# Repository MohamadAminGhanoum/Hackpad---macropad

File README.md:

# Hackpad---macropad
I want to build a hackpad or macropad that i can use when watching yt videos or social media. This will help me for when watching and when editing content.
I have spent around 4.5 hours to do this, it took some time to get used to fusion 360 because it is my first time using it.

Note: there are two distinct files for the .step file, one for the top and one for the bottom

websites used to make the layout of buttons:
https://kbplate.ai03.com/
https://www.keyboard-layout-editor.com/#/

BOM - Components used:
- 4 keys
- 1 xiao rp2040-DIP
- 1 oled panel
- 4 sk6812MINI LEDs
- 1x pcb: price: 1.5 dollar
- 1x soldering iron: price: 2USD

Final look of the macropad:

I rendered the files in fusion 360, and the result is as follows,

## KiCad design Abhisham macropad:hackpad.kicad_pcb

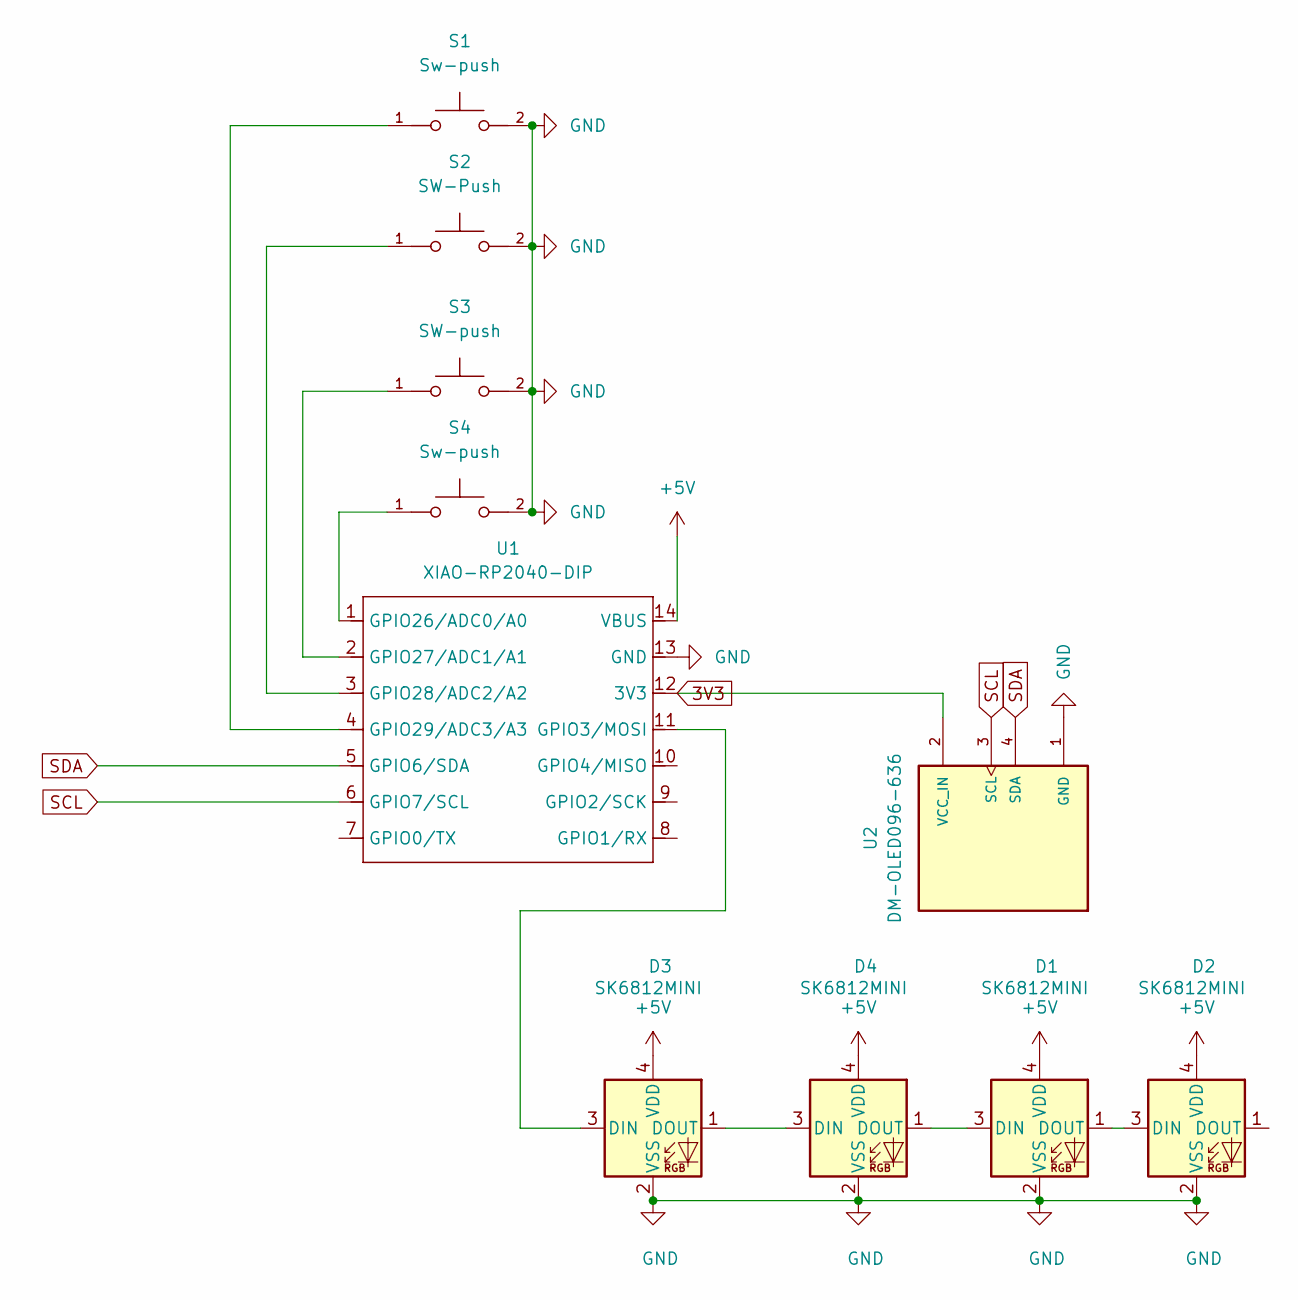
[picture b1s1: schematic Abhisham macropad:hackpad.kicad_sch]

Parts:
D1, D2, D3, D4: SK6812MINI; LED_SK6812MINI_PLCC4_3.5x3.5mm_P1.75mm
S1, S4: Sw-push; SW_Cherry_MX_1.00u_PCB
S2: SW-Push; SW_Cherry_MX_1.00u_PCB
S3: SW-push; SW_Cherry_MX_1.00u_PCB
U1: XIAO-RP2040-DIP
U2: DM-OLED096-636; SSD1306-0.91-OLED-4pin-128x32; PARTREV 2018-09-10

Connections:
3V3: U1.12 (3V3), U2.2 (VCC_IN)
+5V: D1.4 (VDD), D2.4 (VDD), D3.4 (VDD), D4.4 (VDD), U1.14 (VBUS)
GND: D1.2 (VSS), D2.2 (VSS), D3.2 (VSS), D4.2 (VSS), S1.2, S2.2, S3.2, S4.2, U1.13 (GND), U2.1 (GND)
unnamed: D1.3 (DIN), D4.1 (DOUT)
unnamed: D1.1 (DOUT), D2.3 (DIN)
unnamed: D3.3 (DIN), U1.11 (GPIO3/MOSI)
unnamed: D3.1 (DOUT), D4.3 (DIN)
unnamed: S4.1, U1.1 (GPIO26/ADC0/A0)
unnamed: S3.1, U1.2 (GPIO27/ADC1/A1)
unnamed: S2.1, U1.3 (GPIO28/ADC2/A2)
unnamed: S1.1, U1.4 (GPIO29/ADC3/A3)
SCL: U1.6 (GPIO7/SCL), U2.3 (SCL)
SDA: U1.5 (GPIO6/SDA), U2.4 (SDA)

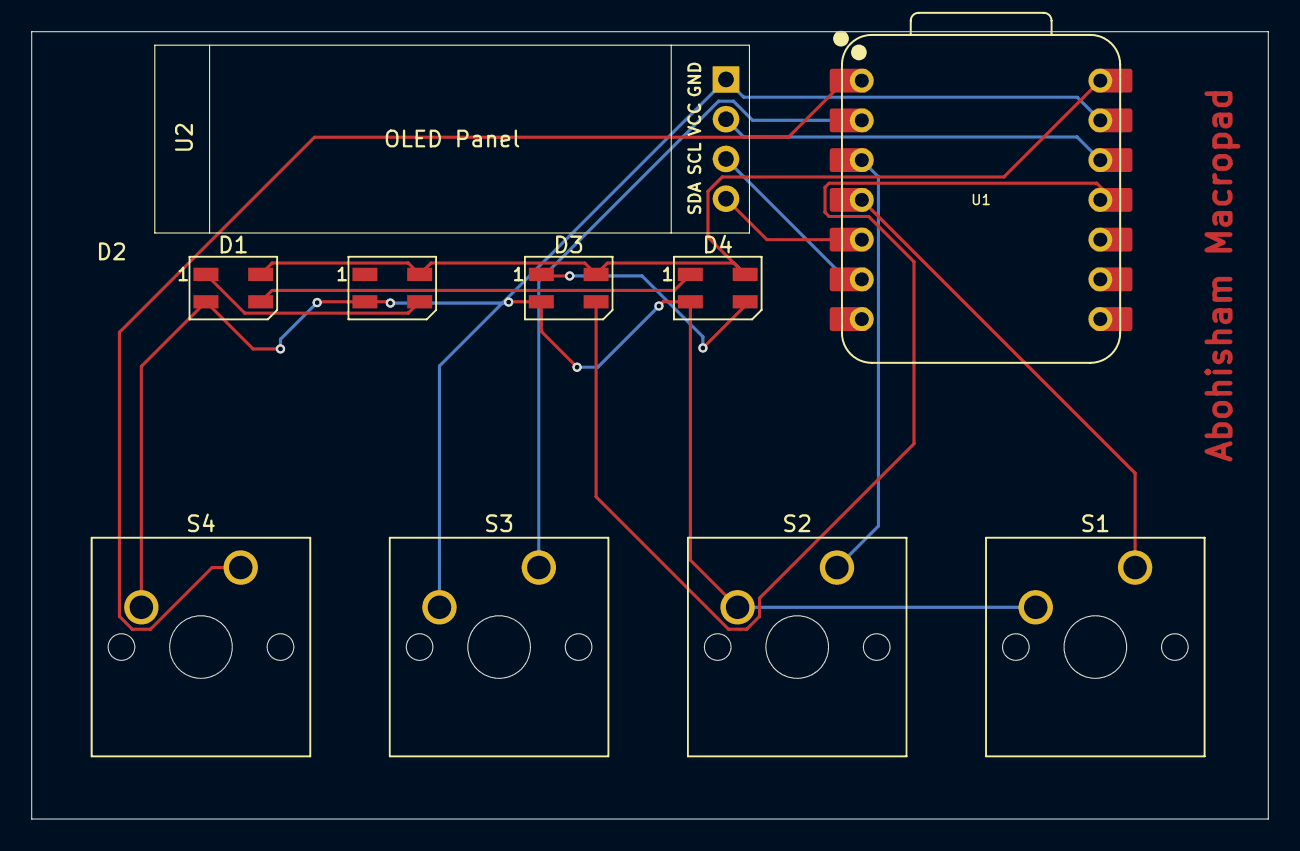
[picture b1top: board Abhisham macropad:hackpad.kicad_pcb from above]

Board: 2 copper layers, 79.0 x 50.3 mm, 10 parts (0 on the bottom side), 13 nets.

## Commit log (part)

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2025-12-26 Update README with BOM and images
    Added a list of components used in the project along with images.
2025-12-26 Update README with PCB price and images
    Added PCB price and images to the README.
2025-12-26 Add initial keyboard configuration and macros
2025-12-26 Rename Abohisham Hackpad - 1.step to Abohisham Hackpad - Bottom- 1.step
2025-12-26 Rename Abohisham - hackpad2.step to Abohisham - hackpad Top 2.step
2025-12-26 Rename Abhisham macropad:hackpad.kicad_pcb to project, Pcb&schematic/Abhisham macropad:hackpad.kicad_pcb
2025-12-26 Rename Abhisham macropad:hackpad.kicad_pro to project,Pcb&schematic/Abhisham macropad:hackpad.kicad_pro
2025-12-26 Rename project,Pcb&schematic/Abhisham macropad:hackpad.kicad_pro to Abhisham macropad:hackpad.kicad_pro
2025-12-26 Rename Abohisham Hackpad - Bottom- 1.step to Case/Abohisham Hackpad - Bottom- 1.step
2025-12-26 Rename Software to Code/Software
2025-12-27 Rename Screenshot 2025-12-27 at 11.45.55.png to assets/Screenshot 2025-12-27 at 11.45.55.png
2025-12-27 Rename Abohisham-macropad Gerber.zip to Gerbers/Abohisham-macropad Gerber.zip
